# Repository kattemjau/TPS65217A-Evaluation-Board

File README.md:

# TPS65217A-Evaluation-Board
TPS65217A Evaluation Board

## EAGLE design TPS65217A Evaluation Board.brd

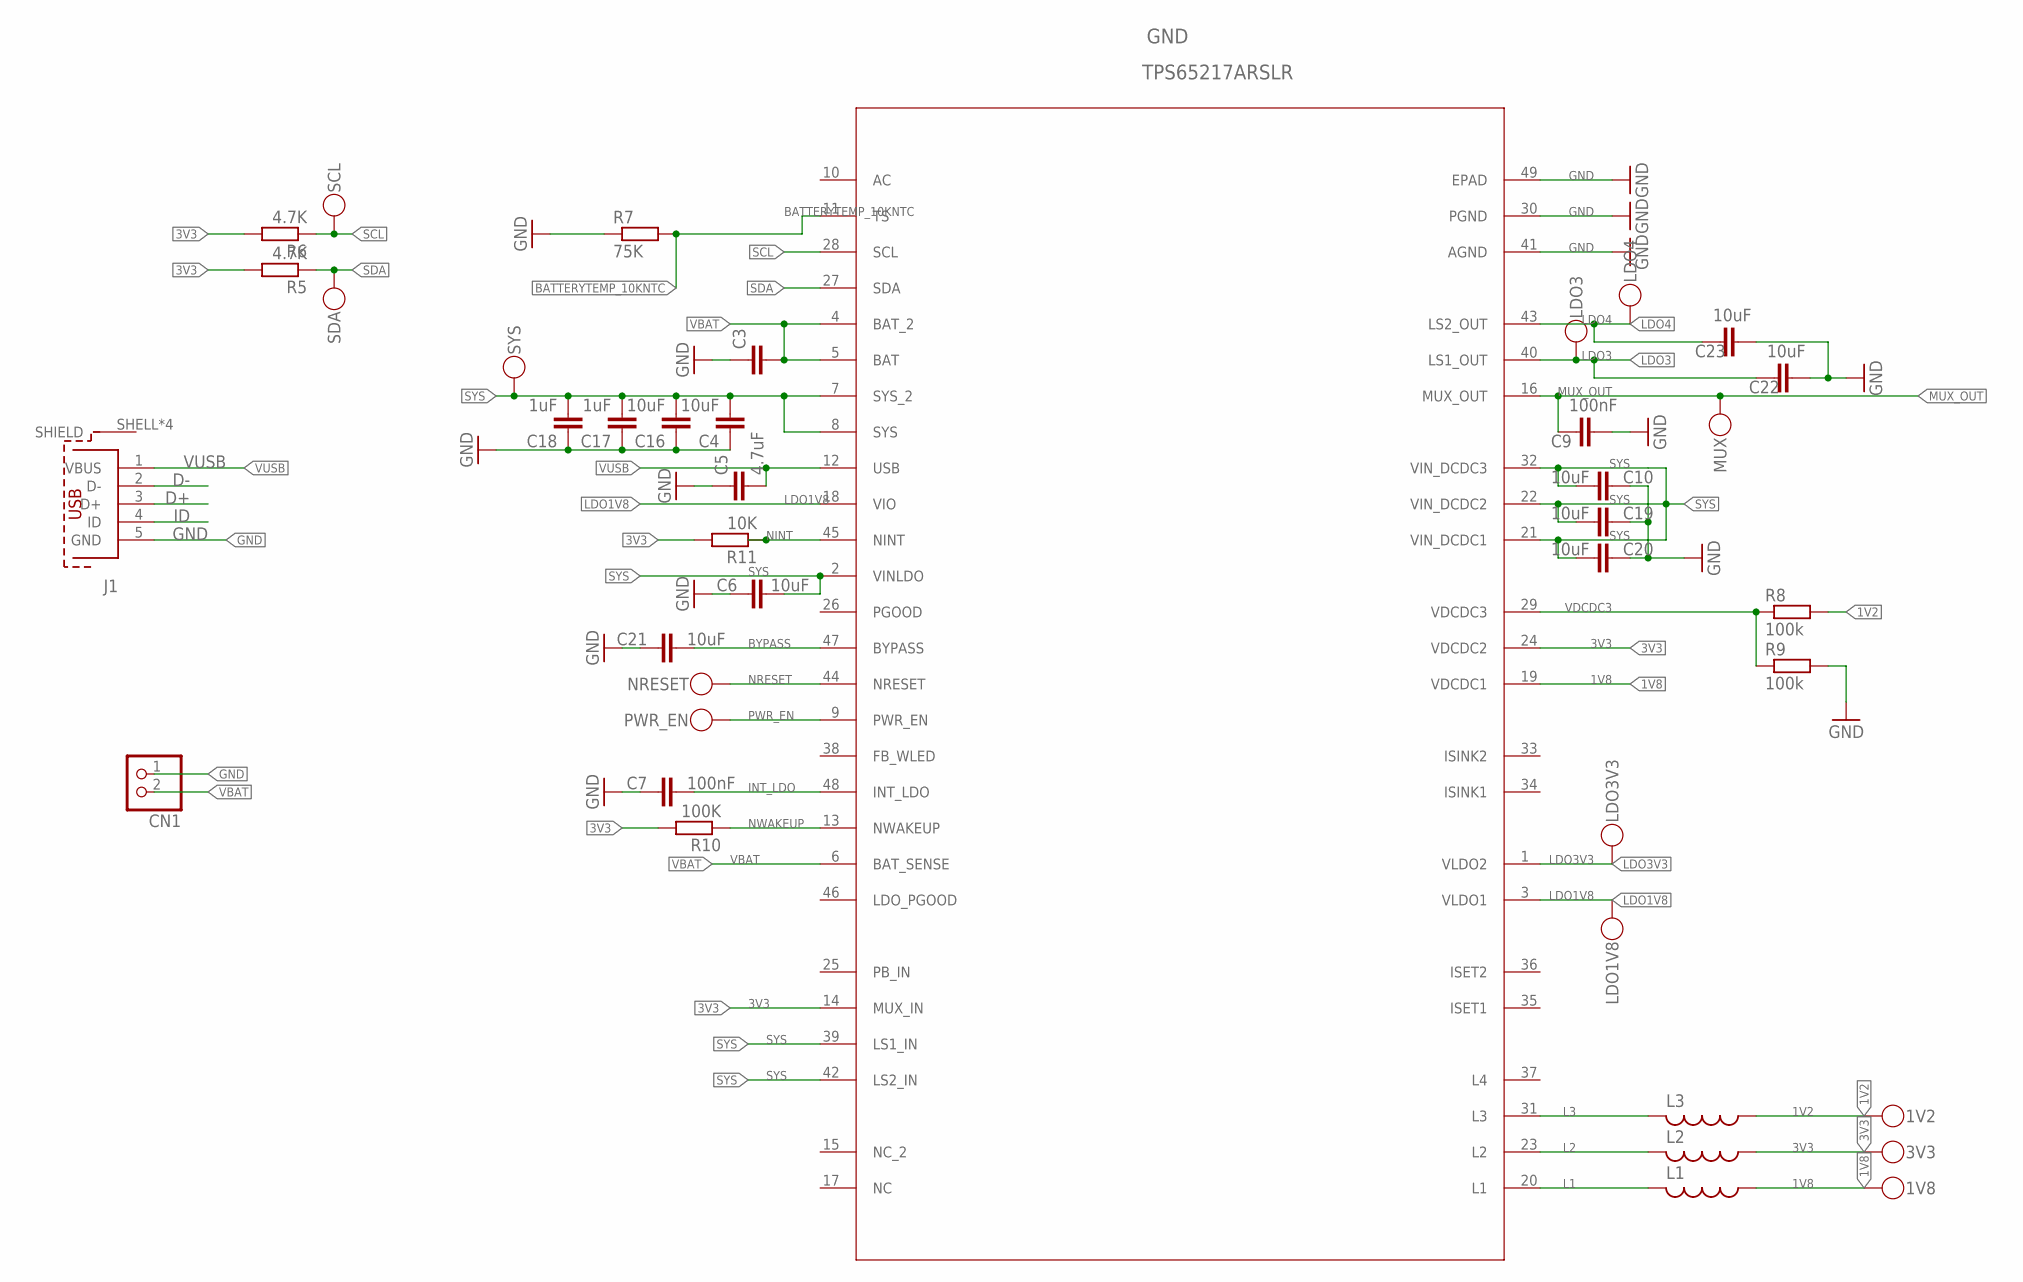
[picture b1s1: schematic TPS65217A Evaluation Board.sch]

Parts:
1V2, 1V8, 3V3: TEST_TESTPOINT
C3: C0603
C4, C6, C10, C16, C19, C20, C21, C22, C23: 10uF; C0603
C5: 4.7uF; C0603
C7, C9: 100nF; C0603
C17, C18: 1uF; C0603
CN1: JST_2PIN-SMT-RA; JST-PH-2-SMT-RA
GND: TPS65217ARSLR; RSL48_4P05X4P05
J1: 629105150521
L1, L2, L3: L4X4; ASPI-4030S-253675
LDO1V8, LDO3, LDO3V3, LDO4: TEST_TESTPOINT
MUX: TEST_TESTPOINT
NRESET: TEST_TESTPOINT
PWR_EN: TEST_TESTPOINT
R5, R6: 4.7K; R0603
R7: 75K; R0603
R8, R9: 100k; R0603
R10: 100K; R0603
R11: 10K; R0603
SCL: TEST_TESTPOINT
SDA: TEST_TESTPOINT
SYS: TEST_TESTPOINT

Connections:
1V2: 1V2.1, L3.P$1 (1), R8.2
1V8: 1V8.1, GND.19 (VDCDC1), L1.P$1 (1)
3V3: 3V3.1, GND.14 (MUX_IN), GND.24 (VDCDC2), L2.P$1 (1), R5.2, R6.2, R10.2, R11.2
BATTERYTEMP_10KNTC: GND.11 (TS), R7.2
BYPASS: C21.2, GND.47 (BYPASS)
D+: J1.3 (D+)
D-: J1.2 (D-)
GND: C3.1, C4.1, C5.1, C6.1, C7.1, C9.1, C10.1, C16.1, C17.1, C18.1, C19.1, C20.1, C21.1, C22.1, C23.1, CN1.1 (2), GND.30 (PGND), GND.41 (AGND), GND.49 (EPAD), J1.5 (GND), R7.1, R9.2
ID: J1.4 (ID)
INT_LDO: C7.2, GND.48 (INT_LDO)
L1: GND.20 (L1), L1.P$2 (2)
L2: GND.23 (L2), L2.P$2 (2)
L3: GND.31 (L3), L3.P$2 (2)
LDO1V8: GND.3 (VLDO1), GND.18 (VIO), LDO1V8.1
LDO3: C22.2, GND.40 (LS1_OUT), LDO3.1
LDO3V3: GND.1 (VLDO2), LDO3V3.1
LDO4: C23.2, GND.43 (LS2_OUT), LDO4.1
MUX_OUT: C9.2, GND.16 (MUX_OUT), MUX.1
NINT: GND.45 (NINT), R11.1
NRESET: GND.44 (NRESET), NRESET.1
NWAKEUP: GND.13 (NWAKEUP), R10.1
PWR_EN: GND.9 (PWR_EN), PWR_EN.1
SCL: GND.28 (SCL), R6.1, SCL.1
SDA: GND.27 (SDA), R5.1, SDA.1
SYS: C4.2, C6.2, C10.2, C16.2, C17.2, C18.2, C19.2, C20.2, GND.2 (VINLDO), GND.7 (SYS_2), GND.8 (SYS), GND.21 (VIN_DCDC1), GND.22 (VIN_DCDC2), GND.32 (VIN_DCDC3), GND.39 (LS1_IN), GND.42 (LS2_IN), SYS.1
VBAT: C3.2, CN1.2 (1), GND.4 (BAT_2), GND.5 (BAT), GND.6 (BAT_SENSE)
VDCDC3: GND.29 (VDCDC3), R8.1, R9.1
VUSB: C5.2, GND.12 (USB), J1.1 (VBUS)

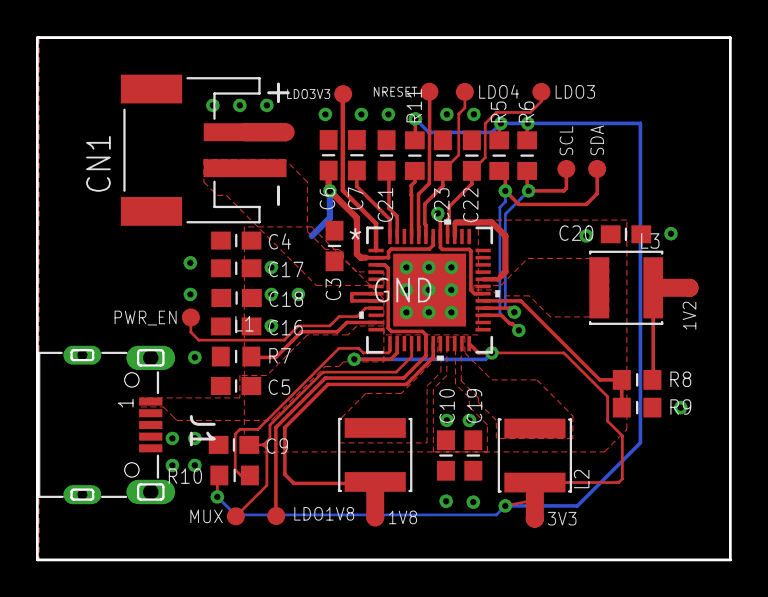
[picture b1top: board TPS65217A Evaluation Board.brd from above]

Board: 2 copper layers, 38.5 x 29.0 mm, 41 parts (1 on the bottom side), 25 nets.

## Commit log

2019-04-26 V1
    Not tested, not finished
2019-04-27 this
2019-04-30 Create LICENSE

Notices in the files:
parts and their libraries:
InputOutputIO: Copyright: Würth Elektronik
